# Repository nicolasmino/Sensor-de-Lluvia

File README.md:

<div align = "center">
</br></br></br>
<h2> Grupo </h2>
<br>
<h3>Este proyecto es una colaboracion entre el grupo CAOS  y un miembro del grupo Black Bull.</h3>
<br><br><br>

</div>
<br><br><br>

<div align = "center">
<h2> Descripción del Proyecto </h2>
</div>
<br>
<p> ¡Bienvenidos al proyecto Sensor de Luvia! este es un sistema de seguridad contra la lluvia con IOT, desarrollado por la colaboración de los grupos Black Bull&CAOS, compuestos por dos estudiantes de 6to año de la EEST N°5 "2 de Abril", los cuales son Nicolas Miño y Lautaro Obregón. 
Este proyecto se encuentra en vía de desarrollo, a su disposicion estan la placa central y su codigo para que funcione con IOT y envie un mensaje a una plataforma en el explorador.
<br><br>
El objetivo principal de ese proyecto es el uso domestico del dispositivo con el fin de resguardar los hogares contra la lluvia cuando el inquilino no está en el, su sistema de seguridad IOT manda un mensaje al una app movil en el celular del inquilino advirtiendo de la lluvia y automaticamente cierra las puertas y ventanas de la casa para así prevenir una inundación o que objetos o dispositivos se mojen.
</p>
<br><br>
<div align = "center">
<h2> Hardware Utilizado </h2>
</div>
<br>
<p> <h3> Modulo & Microprocesador </h3>
- Modulo ESP-WROOM-32, de 38 pines, microprocesador: Tensilica Xtensa LX6.
<br>
<h3> Sensor </h3>
- 1 HW-038
<br>
<h3> Motores & Drivers </h3>
- 2 Motores AP&S SP6 de 260RPM. <br>
- 2 BTS7960 (Drivers de alta potencia).
<br>
<h3> Alimentación & Regulación </h3>
- Bateria recargable de 9V
</p>
<br>
<div align = "center">
<h2> Contribuciones </h2>
</div>
Nos encantaría recibir contribuciones en este y mas proyectos para trabajar juntos, mejorar y ampliar sus capacidades. Si deseas contribuir, por favor abre un "Pull Request" y estaremos encantados de revisarlo.
<br><br>
<div align = "center">
<h2> Info Académica </h2>
</div>
El proyecto Sensor de Lluvia será presentado en la materia Montajes de Proyectos Electrónicos, dirigida por el Ing. Martin Leguizamón. Esta presentación representa una oportunidad para demostrar la creatividad, el trabajo, la evolución y desarrollo del equipo Black Bull&CAOS
<br><br>
<div align = "center">
<h2> Como contactarnos </h2>
</div>
<div align = "center">
<h4> Nicolas Miño (CAOS) : </h4>
</div>
<p align="center">
 <a href="">

 </p>
 <div align = "center">
 <h4> Lautaro Obregón (Black Bull)</h4>
 </div>
 <p align="center">
 <a href="">
 
 </a>
 </p>

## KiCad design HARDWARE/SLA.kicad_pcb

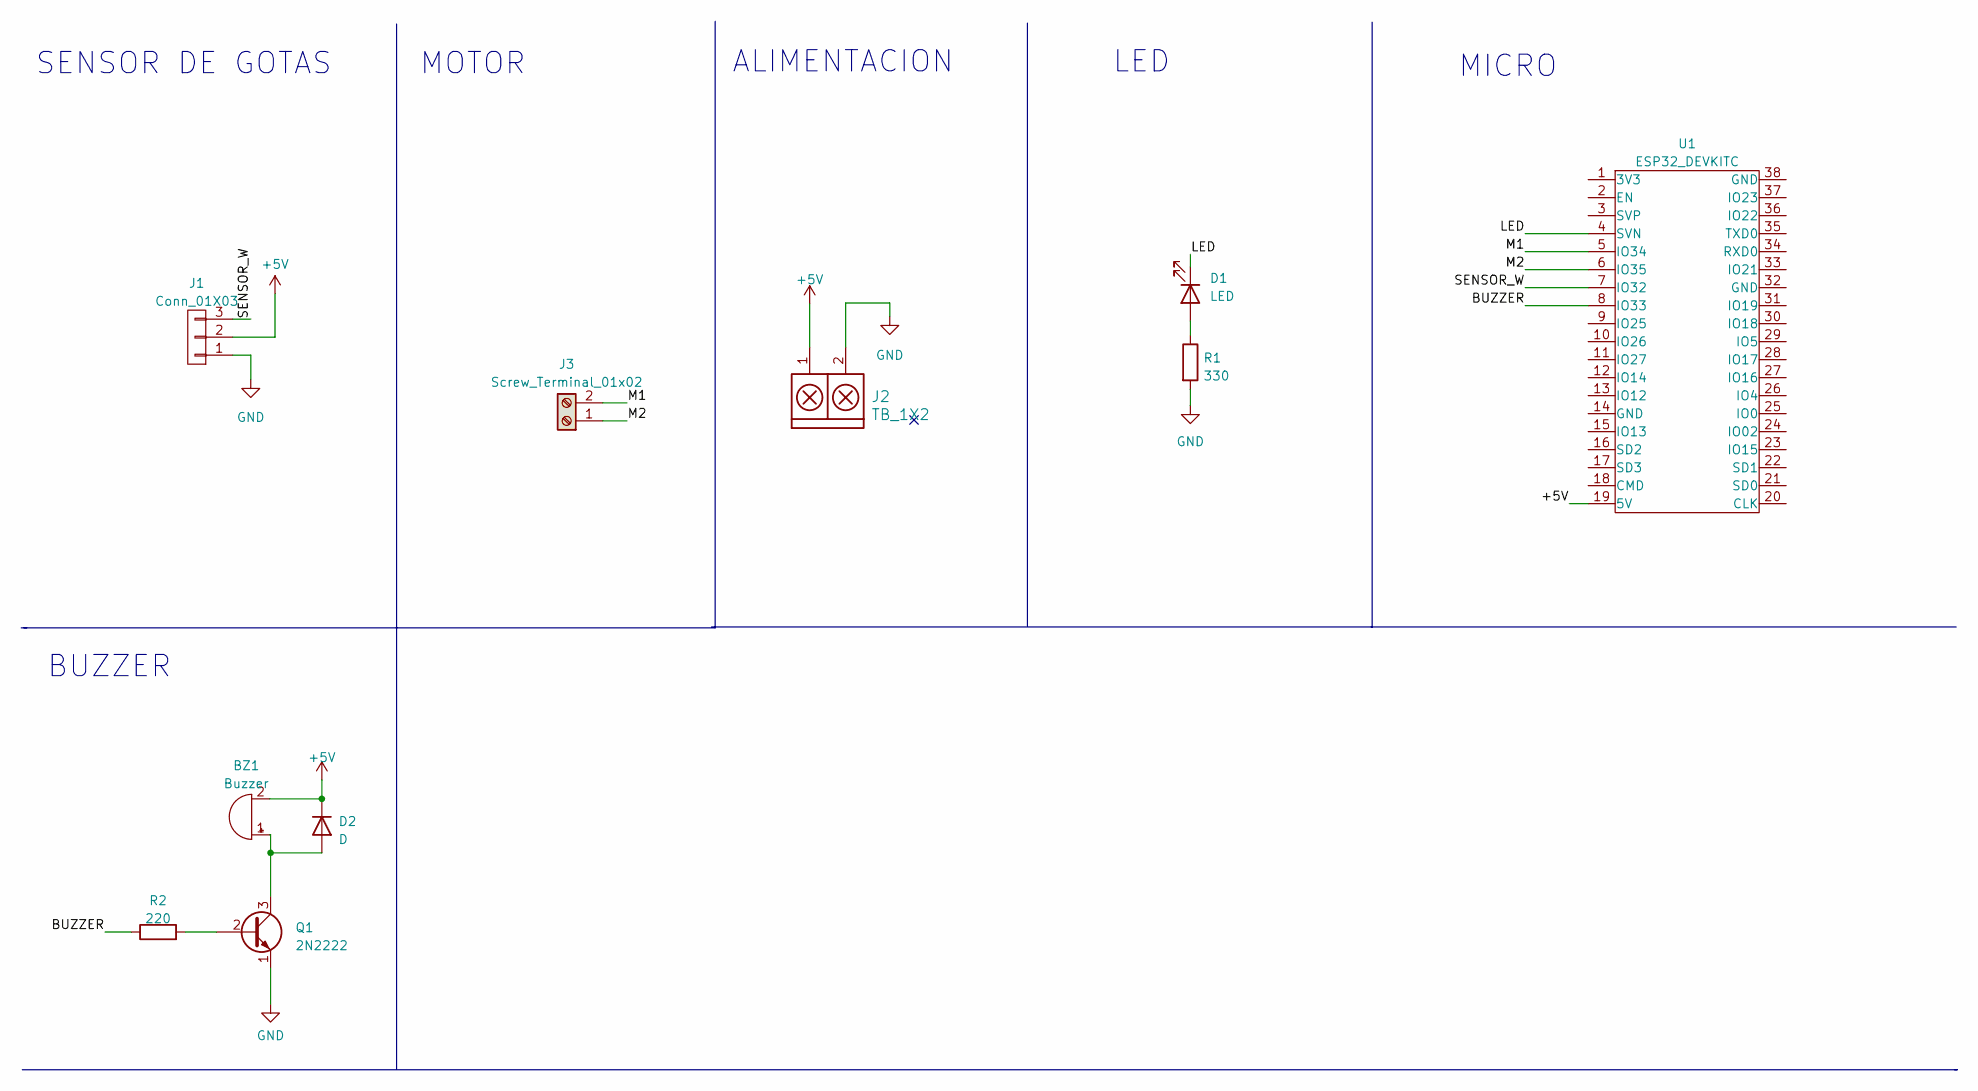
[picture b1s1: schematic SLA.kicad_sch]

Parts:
BZ1: Buzzer; Buzzer_12mm
D1: LED; led_5mm_green
D2: D; D_DO-15_P12.70mm_Horizontal
J1: Conn_01X03; JST_EH_B3B-EH-A_1x03_P2.50mm_Vertical
J2: TB_1X2; BORNERA2_AZUL
J3: Screw_Terminal_01x02; JST_EH_B2B-EH-A_1x02_P2.50mm_Vertical
Q1: 2N2222; to220
R1: 330; RES0.3
R2: 220; RES0.3
U1: ESP32_DEVKITC

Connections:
+5V: BZ1.2 (+), D2.1 (K), J1.2, J2.1, U1.19 (5V)
/BUZZER: R2.1, U1.8 (IO33)
/LED: D1.1 (K), U1.4 (SVN)
/M1: J3.2, U1.5 (IO34)
/M2: J3.1, U1.6 (IO35)
/SENSOR_W: J1.3, U1.7 (IO32)
GND: J1.1, J2.2, Q1.1 (E), R1.2
unnamed: BZ1.1 (-), D2.2 (A), Q1.3 (C)
unnamed: D1.2 (A), R1.1
unnamed: Q1.2 (B), R2.2

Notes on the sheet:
BUZZER
ALIMENTACION
SENSOR DE GOTAS
MICRO
MOTOR
LED

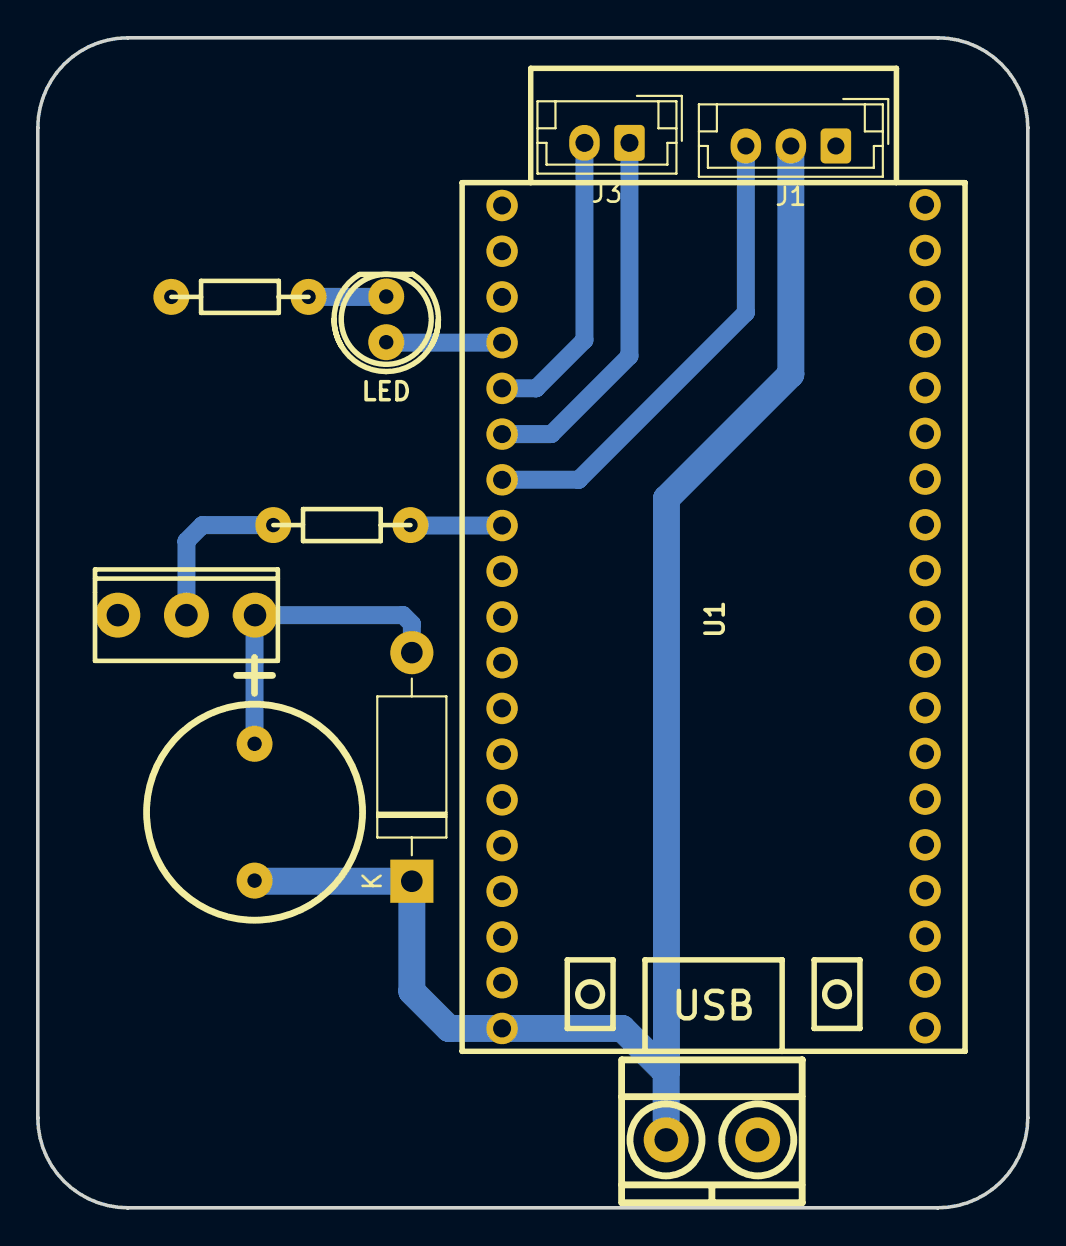
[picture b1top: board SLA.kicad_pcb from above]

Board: 2 copper layers, 55.0 x 65.0 mm, 10 parts (0 on the bottom side), 10 nets.

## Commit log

2023-11-27 SENSOR DE LLUVIA
